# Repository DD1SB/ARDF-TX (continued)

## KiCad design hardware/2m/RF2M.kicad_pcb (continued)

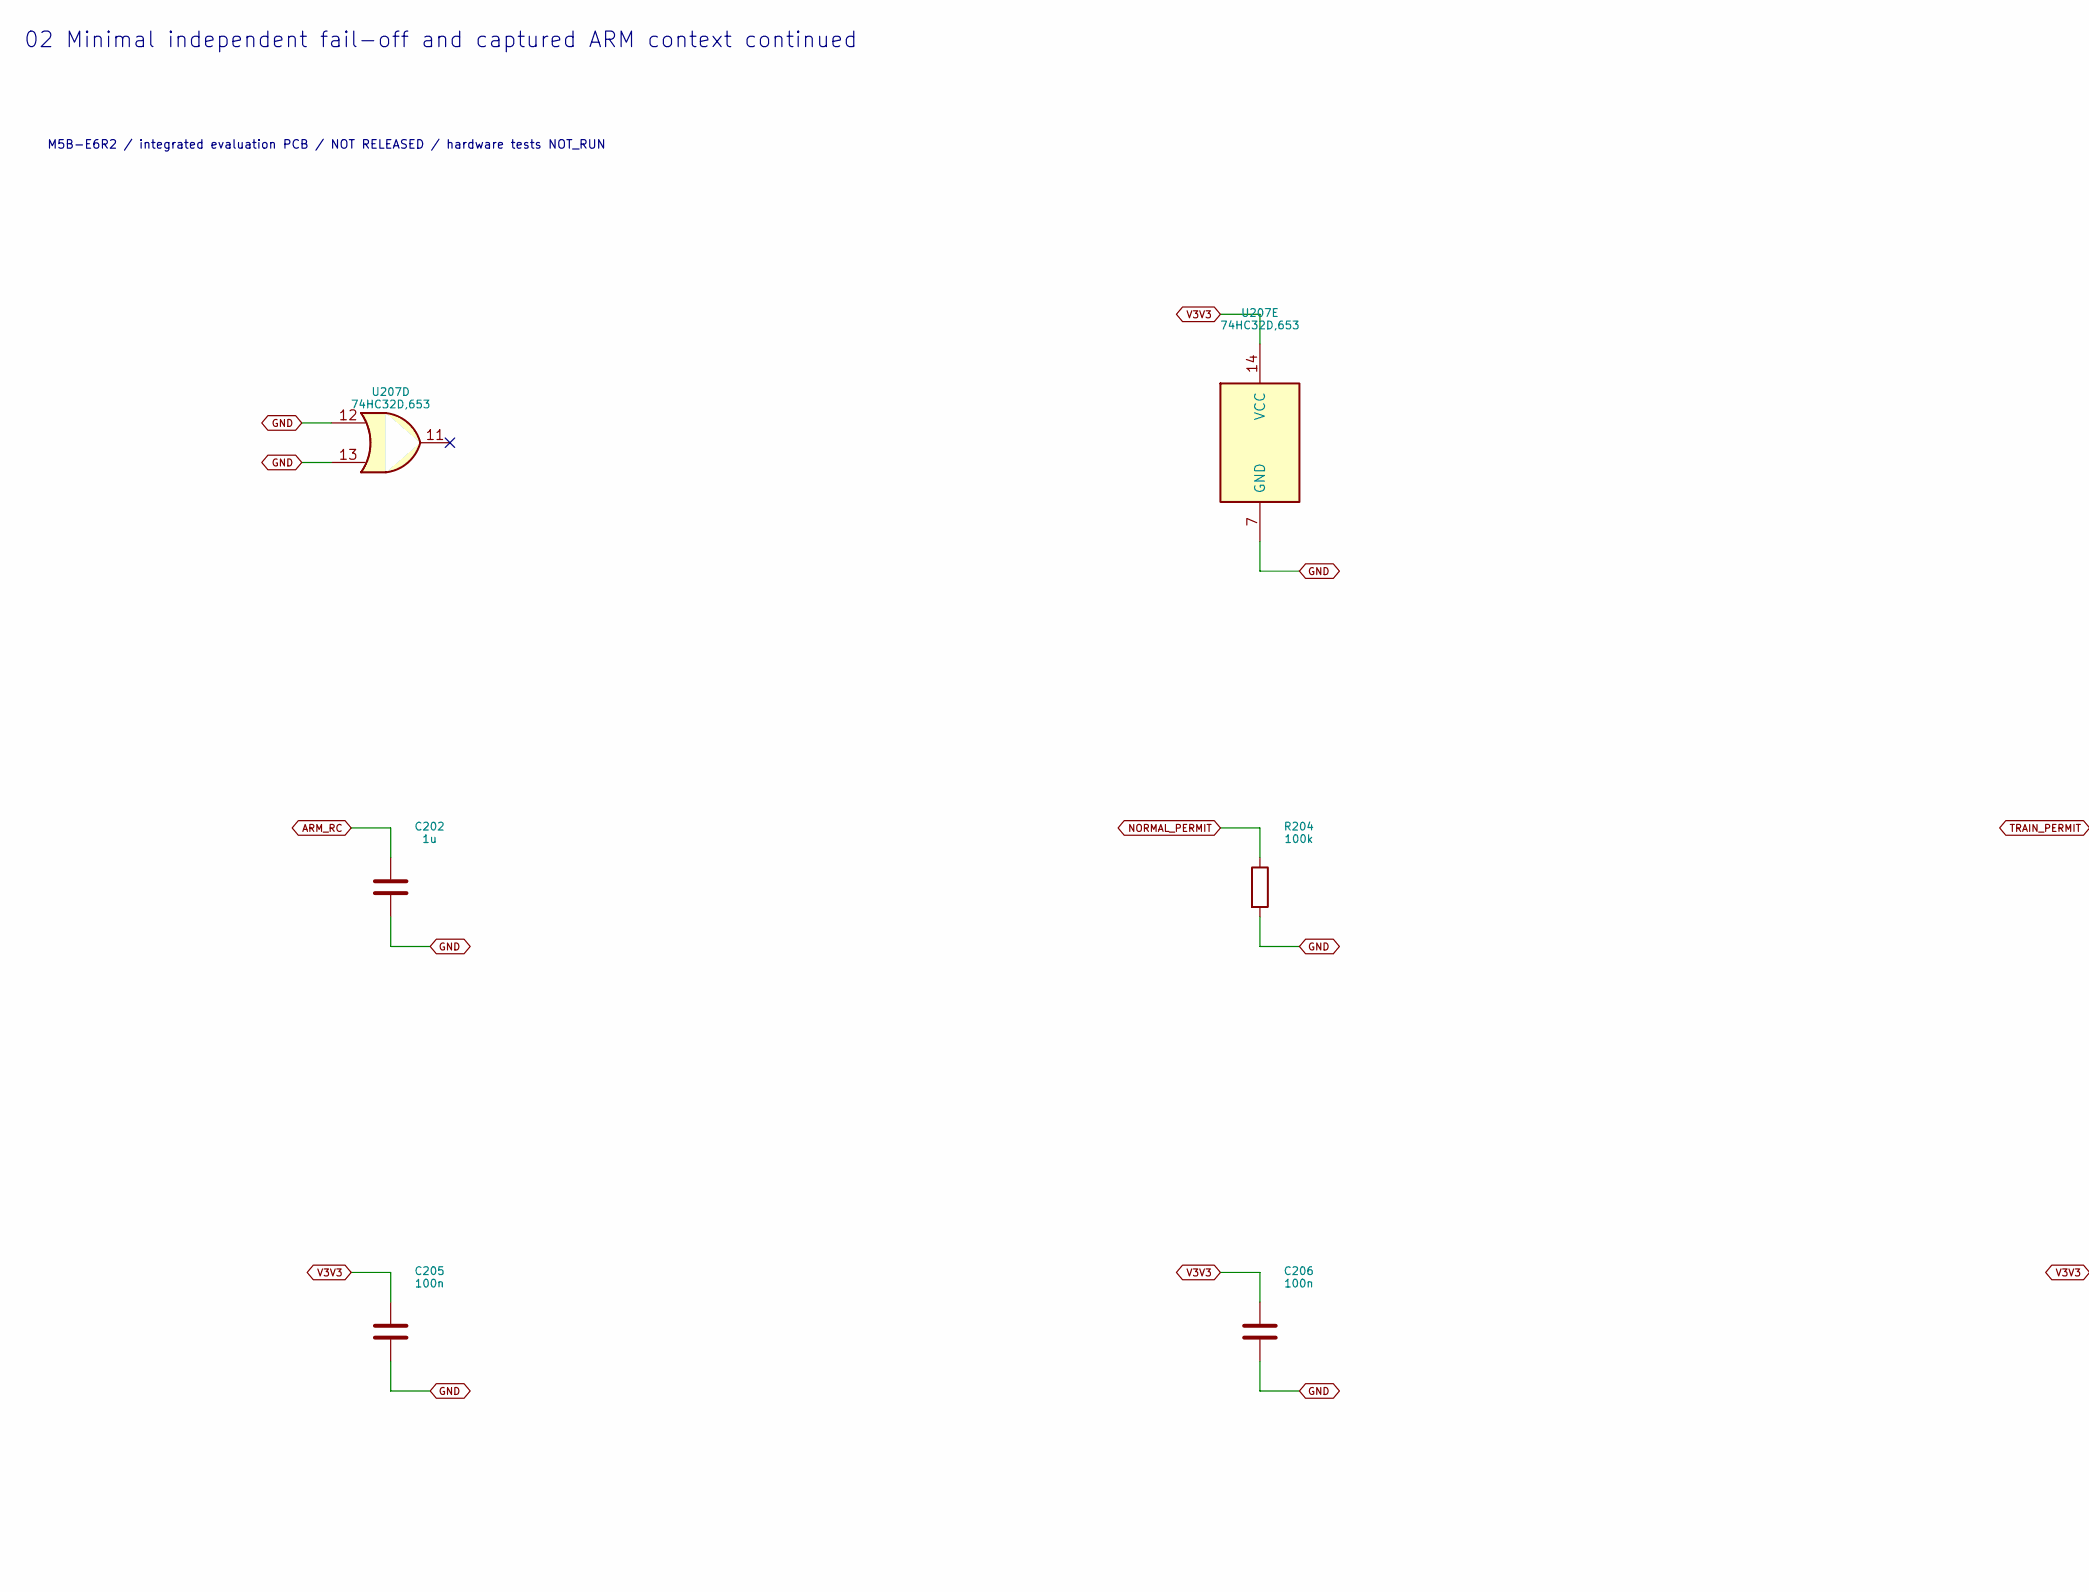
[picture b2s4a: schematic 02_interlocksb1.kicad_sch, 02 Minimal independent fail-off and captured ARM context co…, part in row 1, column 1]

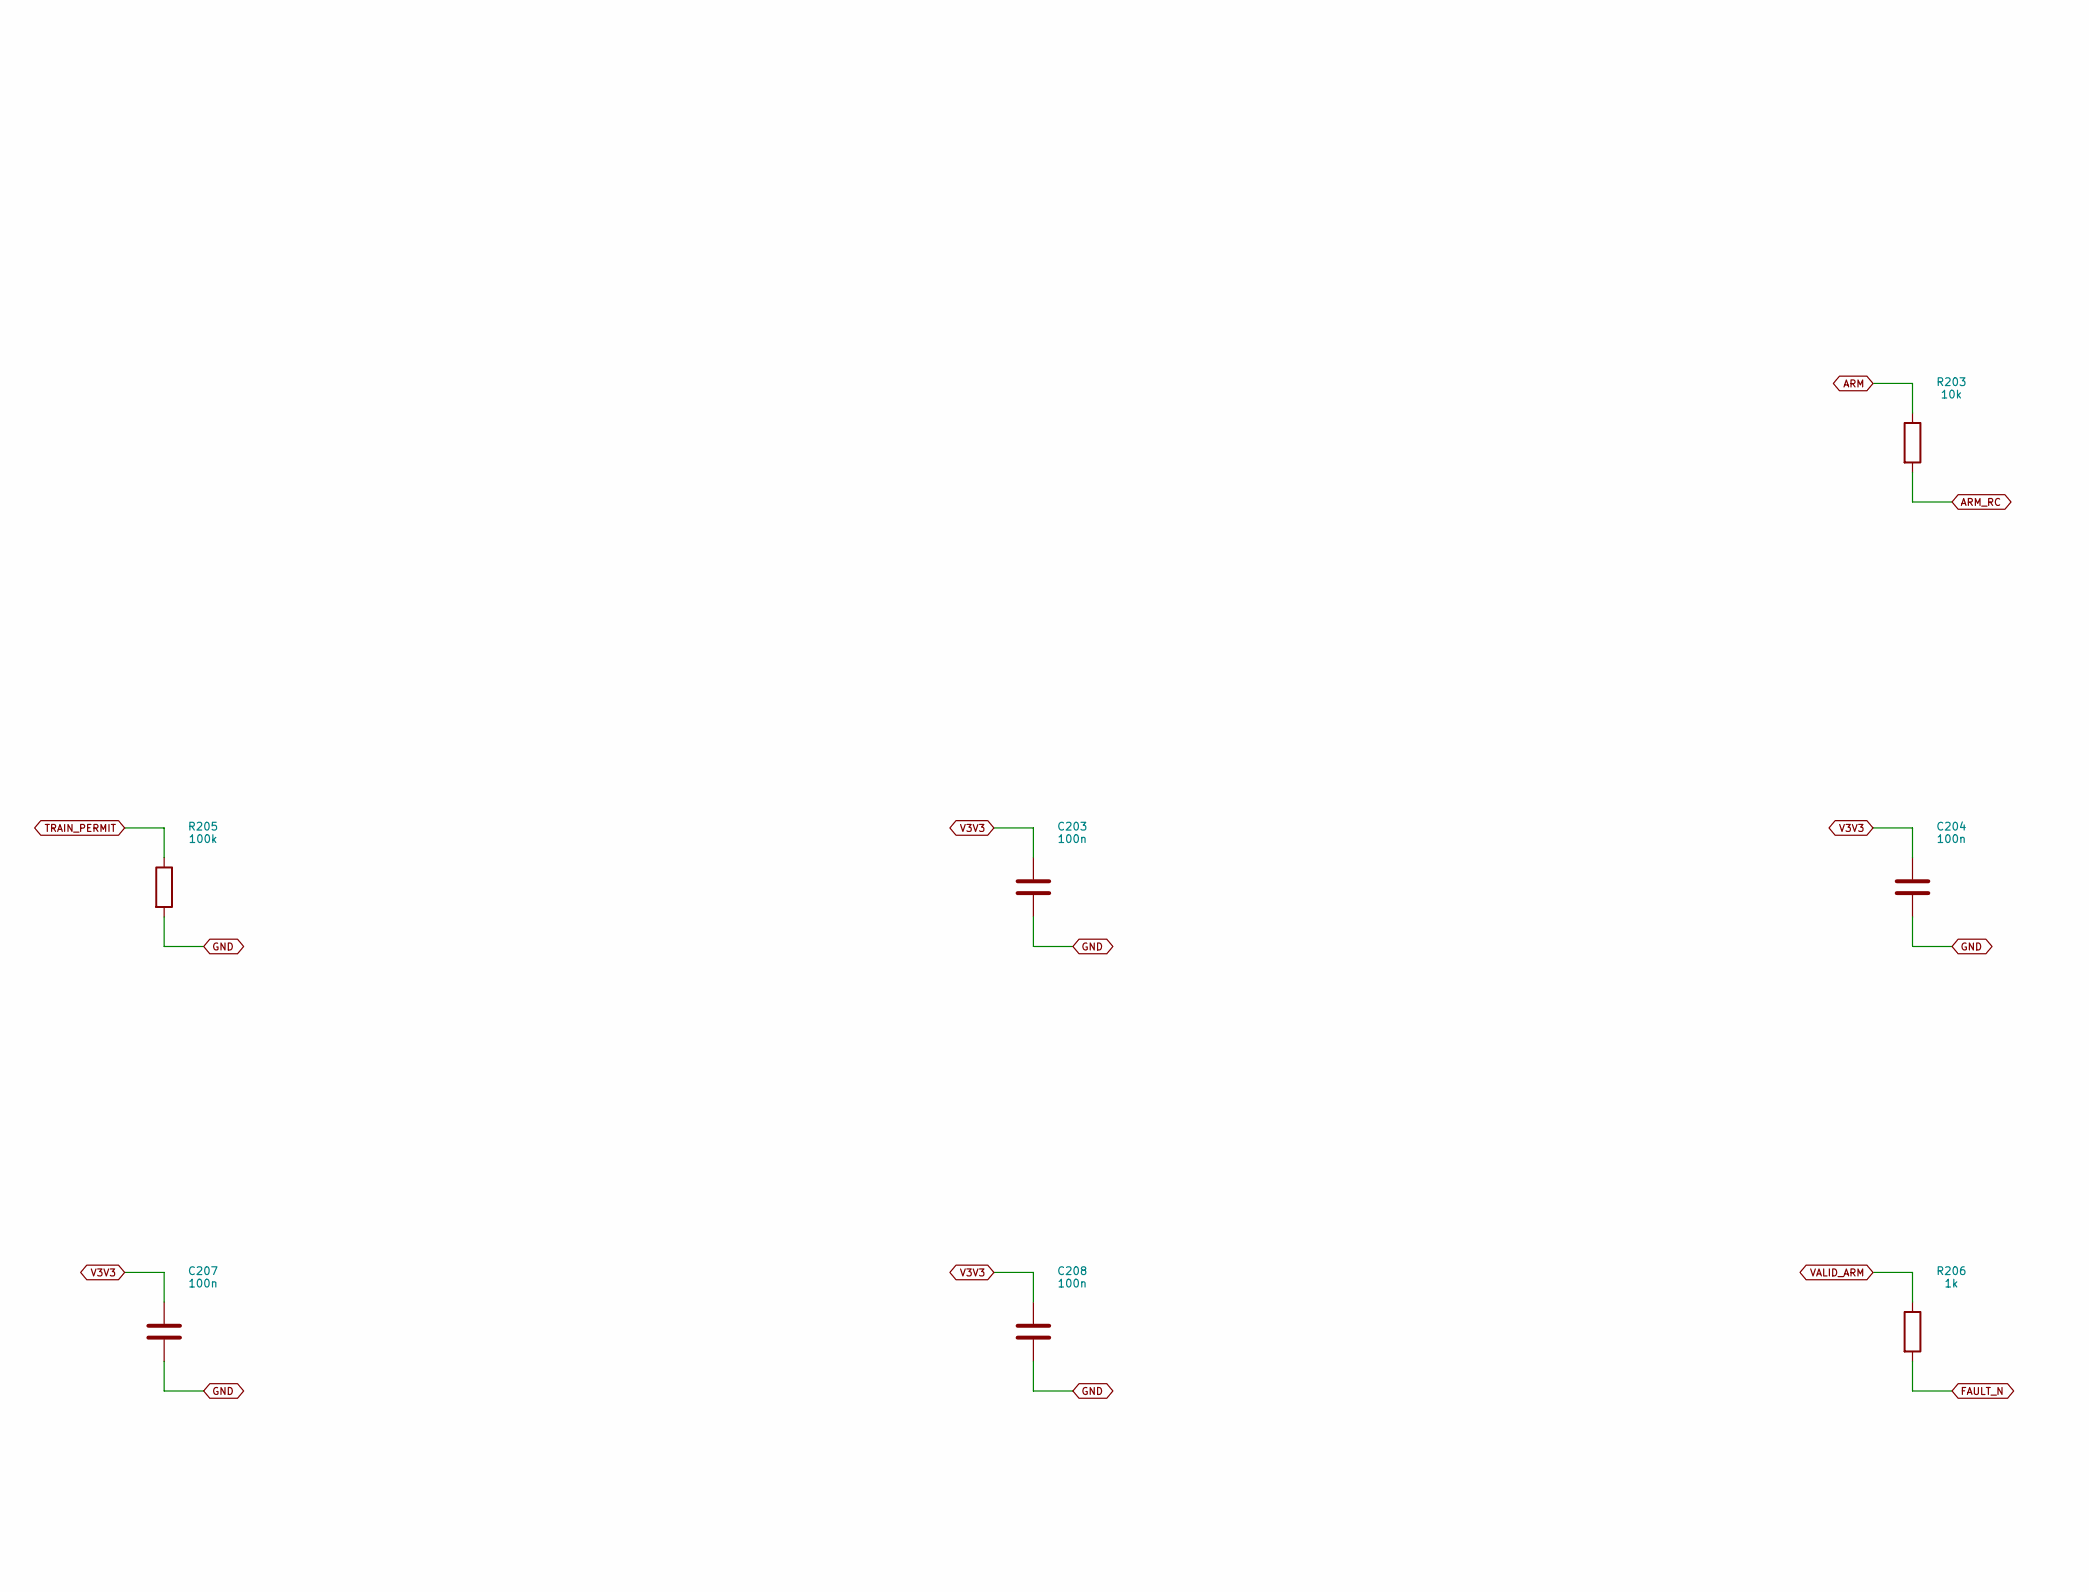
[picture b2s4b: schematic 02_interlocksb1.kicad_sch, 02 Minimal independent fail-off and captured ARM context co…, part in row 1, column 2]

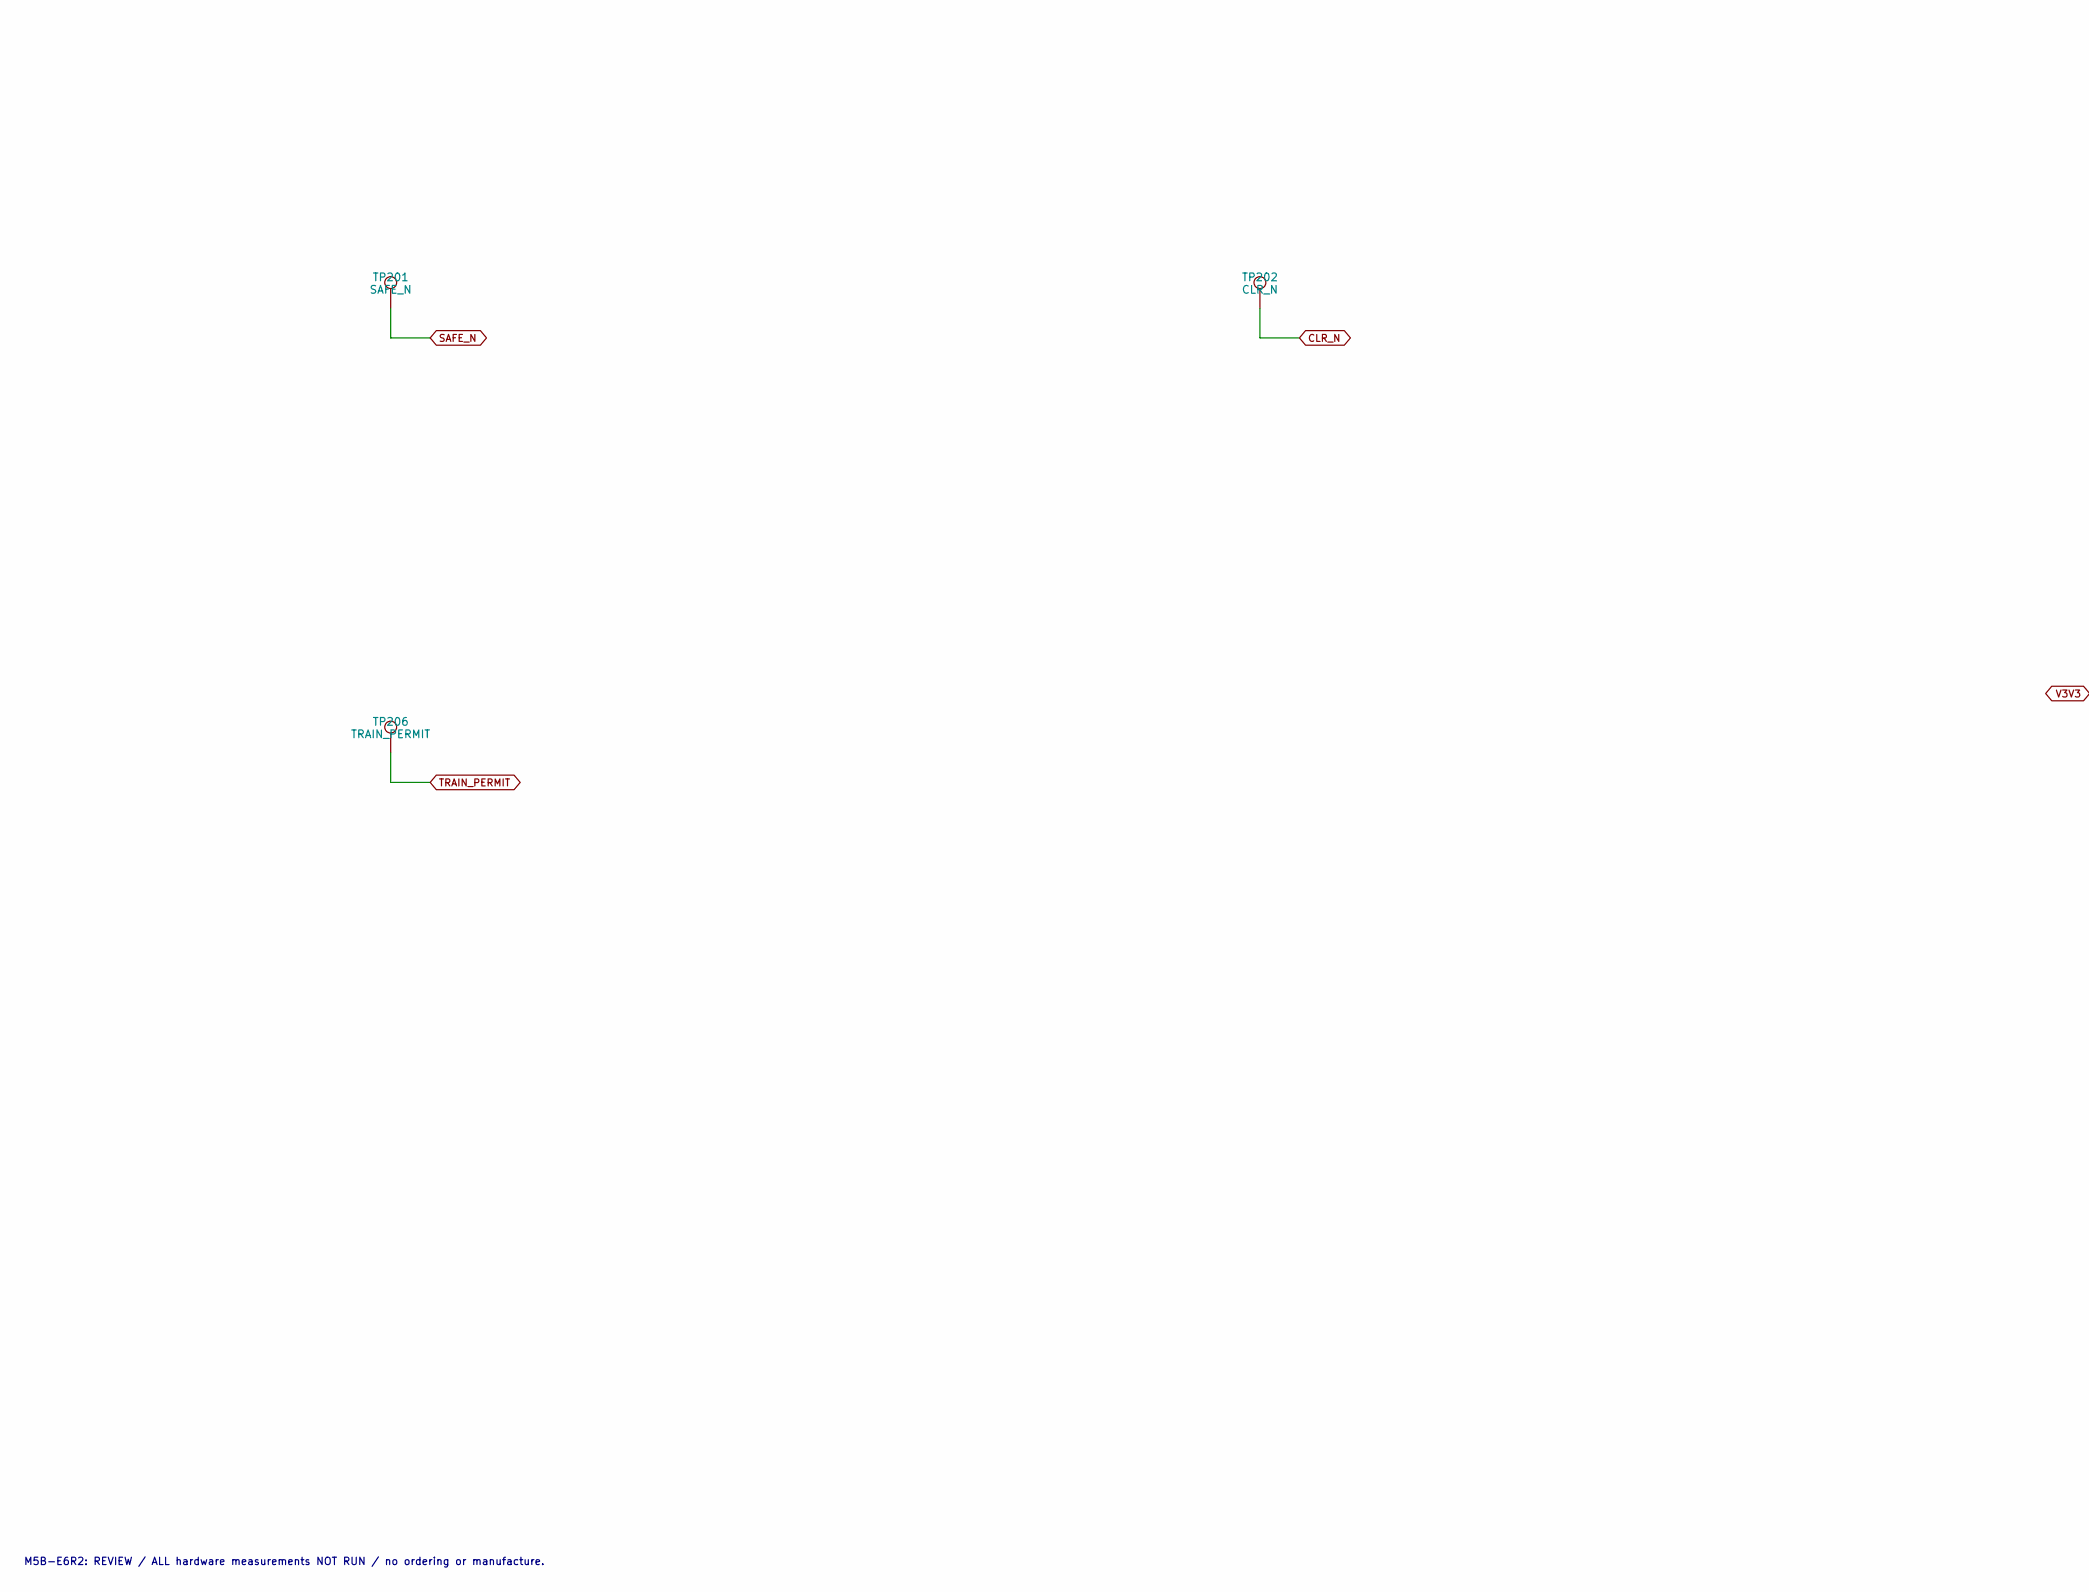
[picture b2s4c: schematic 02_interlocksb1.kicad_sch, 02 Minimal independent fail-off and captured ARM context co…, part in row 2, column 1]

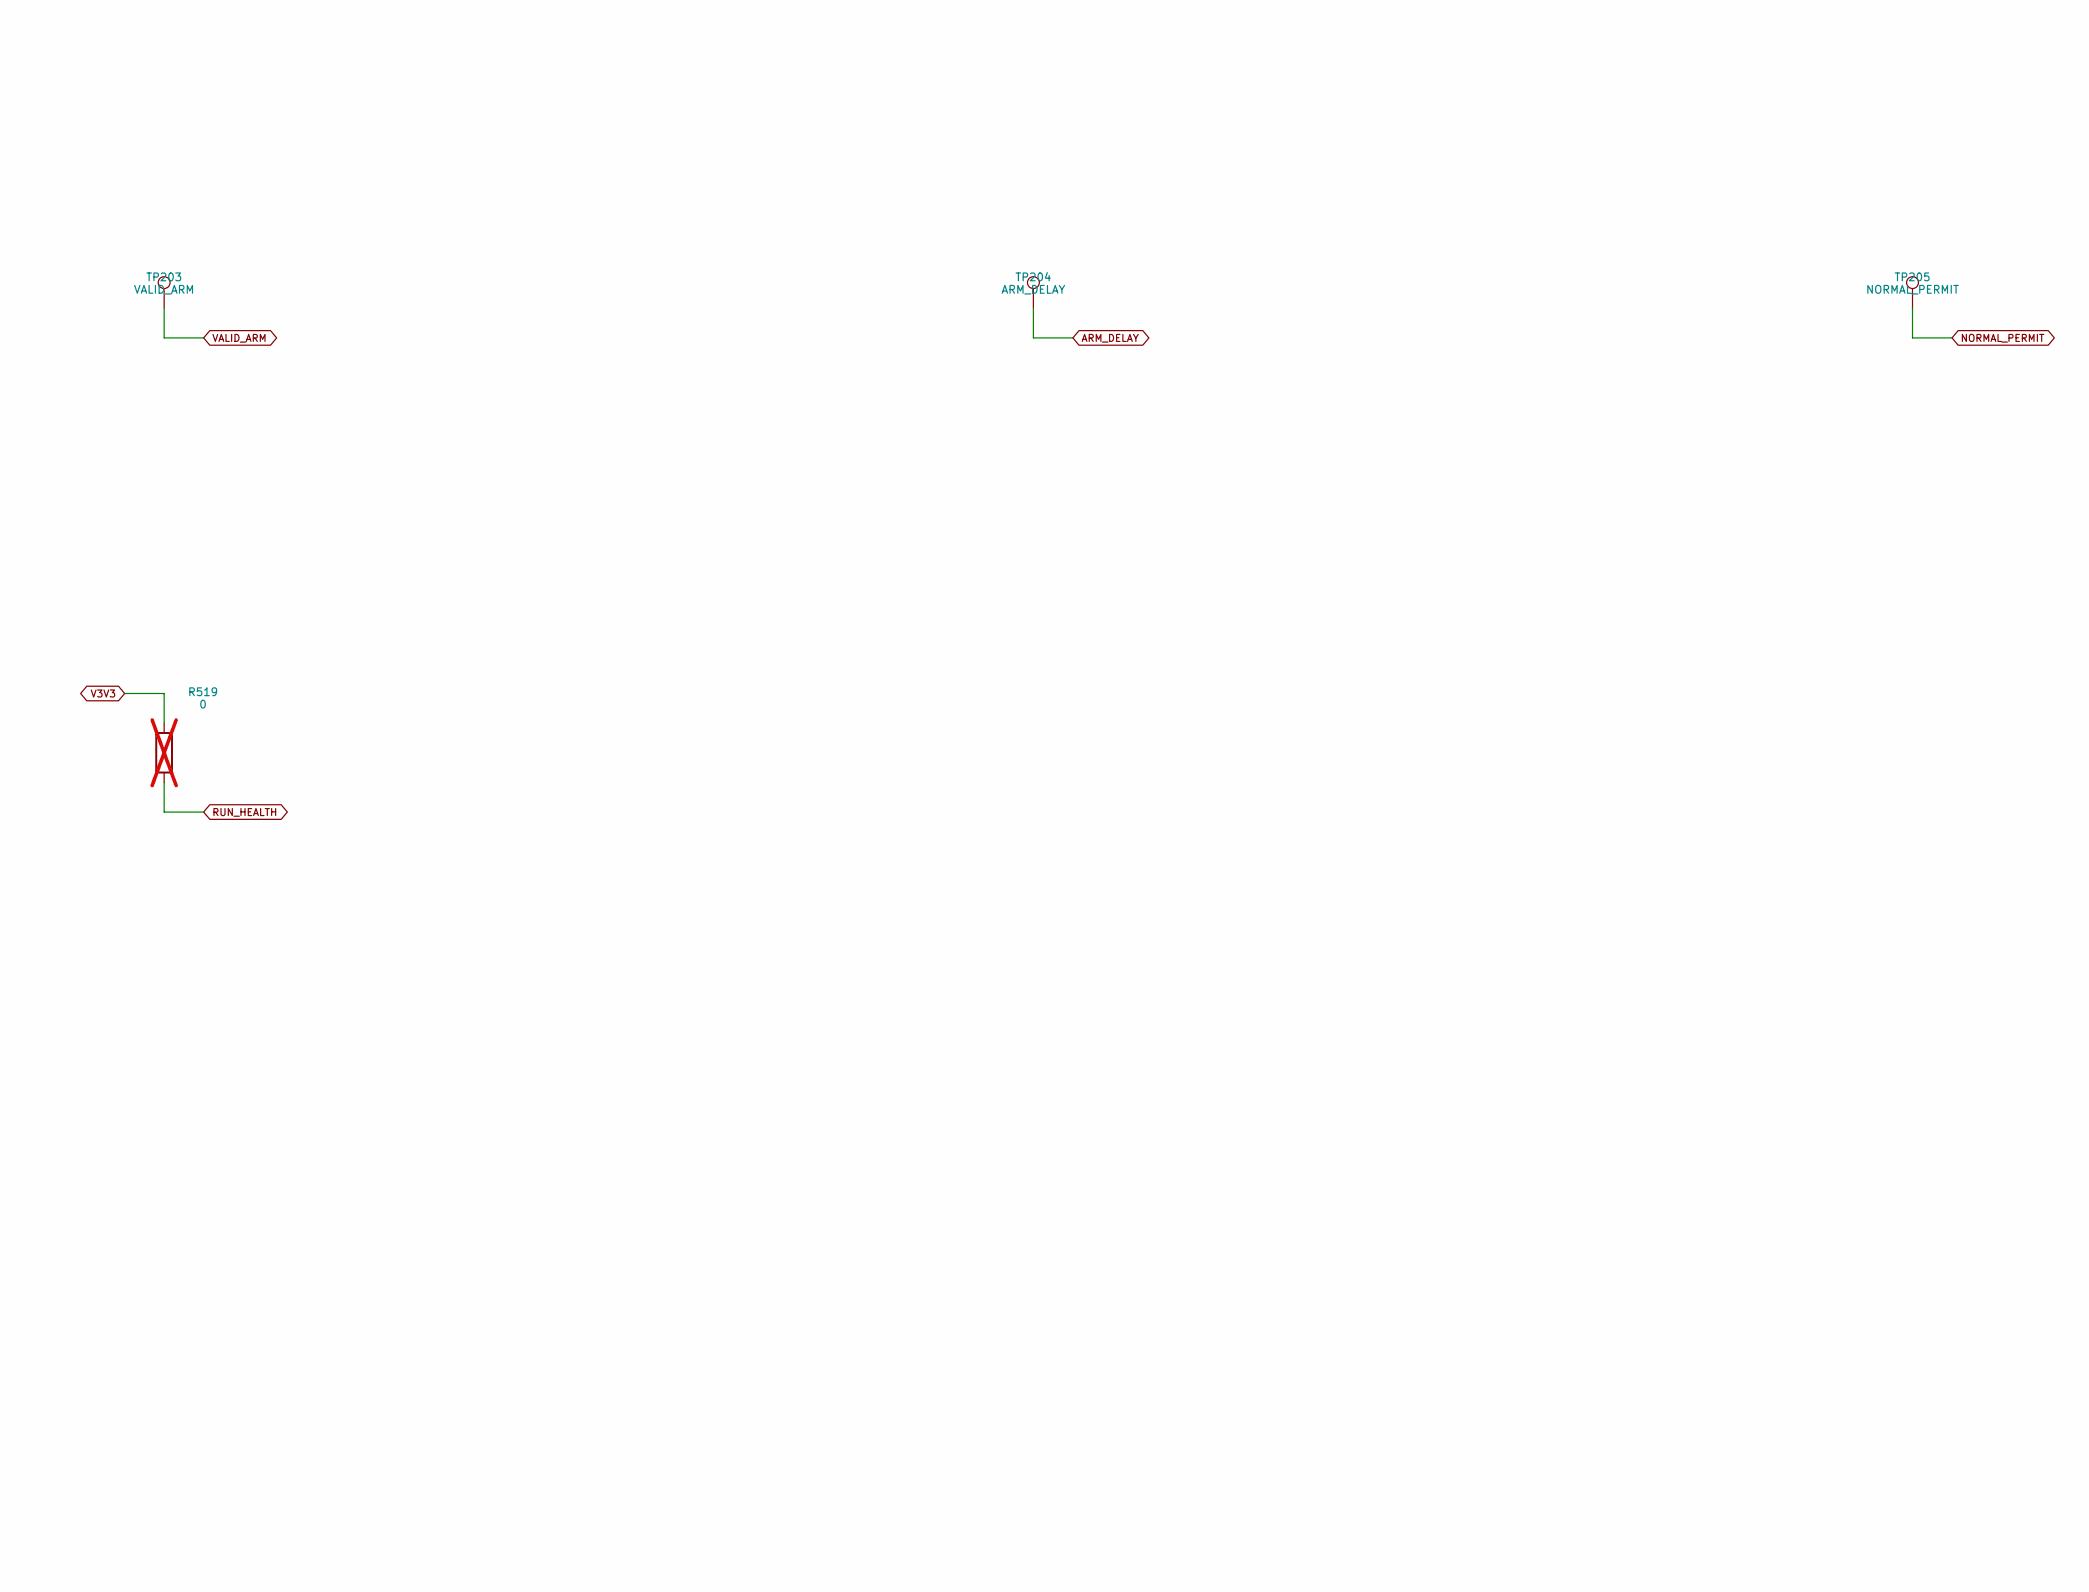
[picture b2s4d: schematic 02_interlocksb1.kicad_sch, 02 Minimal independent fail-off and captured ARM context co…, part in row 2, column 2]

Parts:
C202: 1u; C_0805_2012Metric_E3; MPN CC0805KKX7R9BB105
C203, C204, C205, C206, C207, C208: 100n; C_0603_1608Metric_E3; MPN CC0603KRX7R8BB104
R203: 10k; R_0603_1608Metric_E3; MPN RC0603FR-0710KL
R204, R205: 100k; R_0603_1608Metric_E3; MPN RC0603FR-07100KL
R206: 1k; R_0603_1608Metric_E3; MPN RC0603FR-071KL
R519: 0; R_0603_1608Metric_E3; MPN RC0603JR-070RL; not fitted
TP201: SAFE_N; TestPoint_Pad_D1.0mm_E3; MPN PCB feature
TP202: CLR_N; TestPoint_Pad_D1.0mm_E3; MPN PCB feature
TP203: VALID_ARM; TestPoint_Pad_D1.0mm_E3; MPN PCB feature
TP204: ARM_DELAY; TestPoint_Pad_D1.0mm_E3; MPN PCB feature
TP205: NORMAL_PERMIT; TestPoint_Pad_D1.0mm_E3; MPN PCB feature
TP206: TRAIN_PERMIT; TestPoint_Pad_D1.0mm_E3; MPN PCB feature
U207: 74HC32D,653; SOIC-14_3.9x8.7mm_P1.27mm_E3; MPN 74HC32D,653

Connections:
ARM: R203.1; also elsewhere on the board
ARM_DELAY: TP204.1; also elsewhere on the board
ARM_RC: C202.1, R203.2; also elsewhere on the board
CLR_N: TP202.1; also elsewhere on the board
FAULT_N: R206.2; also elsewhere on the board
GND: C202.2, C203.2, C204.2, C205.2, C206.2, C207.2, C208.2, R204.2, R205.2, U207.7 (GND), U207.12, U207.13; also elsewhere on the board
NORMAL_PERMIT: R204.1, TP205.1; also elsewhere on the board
RUN_HEALTH: R519.2; also elsewhere on the board
SAFE_N: TP201.1; also elsewhere on the board
TRAIN_PERMIT: R205.1, TP206.1; also elsewhere on the board
V3V3: C203.1, C204.1, C205.1, C206.1, C207.1, C208.1, R519.1, U207.14 (VCC); also elsewhere on the board
VALID_ARM: R206.1, TP203.1; also elsewhere on the board

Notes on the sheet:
02 Minimal independent fail-off and captured ARM context continued
M5B-E6R2 / integrated evaluation PCB / NOT RELEASED / hardware tests NOT_RUN
M5B-E6R2: REVIEW / ALL hardware measurements NOT RUN / no ordering or manufacture.
